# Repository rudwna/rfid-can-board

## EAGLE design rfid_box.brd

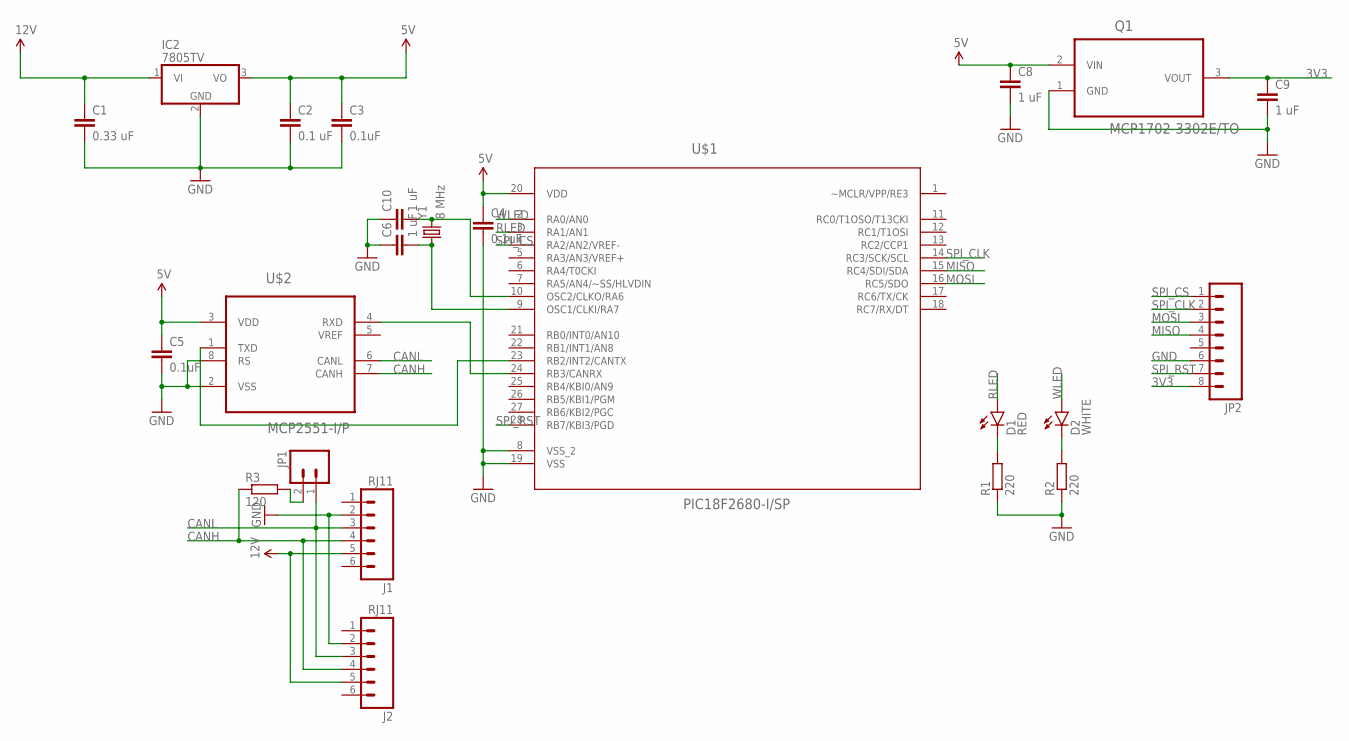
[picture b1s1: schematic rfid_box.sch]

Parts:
C1: 0.33 uF; C050-030X075
C2: 0.1 uF; C050-030X075
C3, C4, C5: 0.1uF; C050-030X075
C6, C10: 1 uF; C025-025X050
C8, C9: 1 uF; C050-030X075
D1: RED; LED5MM
D2: WHITE; LED5MM
IC2: 7805TV; TO220V
J1, J2: RJ11; RJ11-6
JP1: M02PTH; 1X02
JP2: M08; 1X08_ROUND
Q1: MCP1702-3302E/TO; TO127P254X533-3
R1, R2: 220; 0207/10
R3: 120; 0207/10
U$1: PIC18F2680-I/SP; DIP254P762X508-28
U$2: MCP2551-I/P; DIP254P762X432-8
Y1: 8 MHz; HC49US

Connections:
3V3: C9.1, JP2.8, Q1.3 (VOUT)
5V: C2.1, C3.1, C4.1, C5.1, C8.1, IC2.3 (VO), Q1.2 (VIN), U$1.20 (VDD), U$2.3 (VDD)
12V: C1.1, IC2.1 (VI), J1.5, J2.5
CANH: J1.4, J2.4, R3.1, U$2.7 (CANH)
CANL: J1.3, J2.3, JP1.1, U$2.6 (CANL)
GND: C1.2, C2.2, C3.2, C4.2, C5.2, C6.1, C8.2, C9.2, C10.1, IC2.2 (GND), J1.2, J2.2, JP2.6, Q1.1 (GND), R1.1, R2.1, U$1.8 (VSS_2), U$1.19 (VSS), U$2.2 (VSS), U$2.8 (RS)
MISO: JP2.4, U$1.15 (RC4/SDI/SDA)
MOSI: JP2.3, U$1.16 (RC5/SDO)
unnamed: U$1.24 (RB3/CANRX), U$2.4 (RXD)
unnamed: U$1.23 (RB2/INT2/CANTX), U$2.1 (TXD)
unnamed: C10.2, U$1.10 (OSC2/CLKO/RA6), Y1.2
unnamed: C6.2, U$1.9 (OSC1/CLKI/RA7), Y1.1
unnamed: D1.K (C), R1.2
unnamed: D2.K (C), R2.2
unnamed: JP1.2, R3.2
RLED: D1.A, U$1.3 (RA1/AN1)
SPI_CLK: JP2.2, U$1.14 (RC3/SCK/SCL)
SPI_CS: JP2.1, U$1.4 (RA2/AN2/VREF-)
SPI_RST: JP2.7, U$1.28 (RB7/KBI3/PGD)
WLED: D2.A, U$1.2 (RA0/AN0)

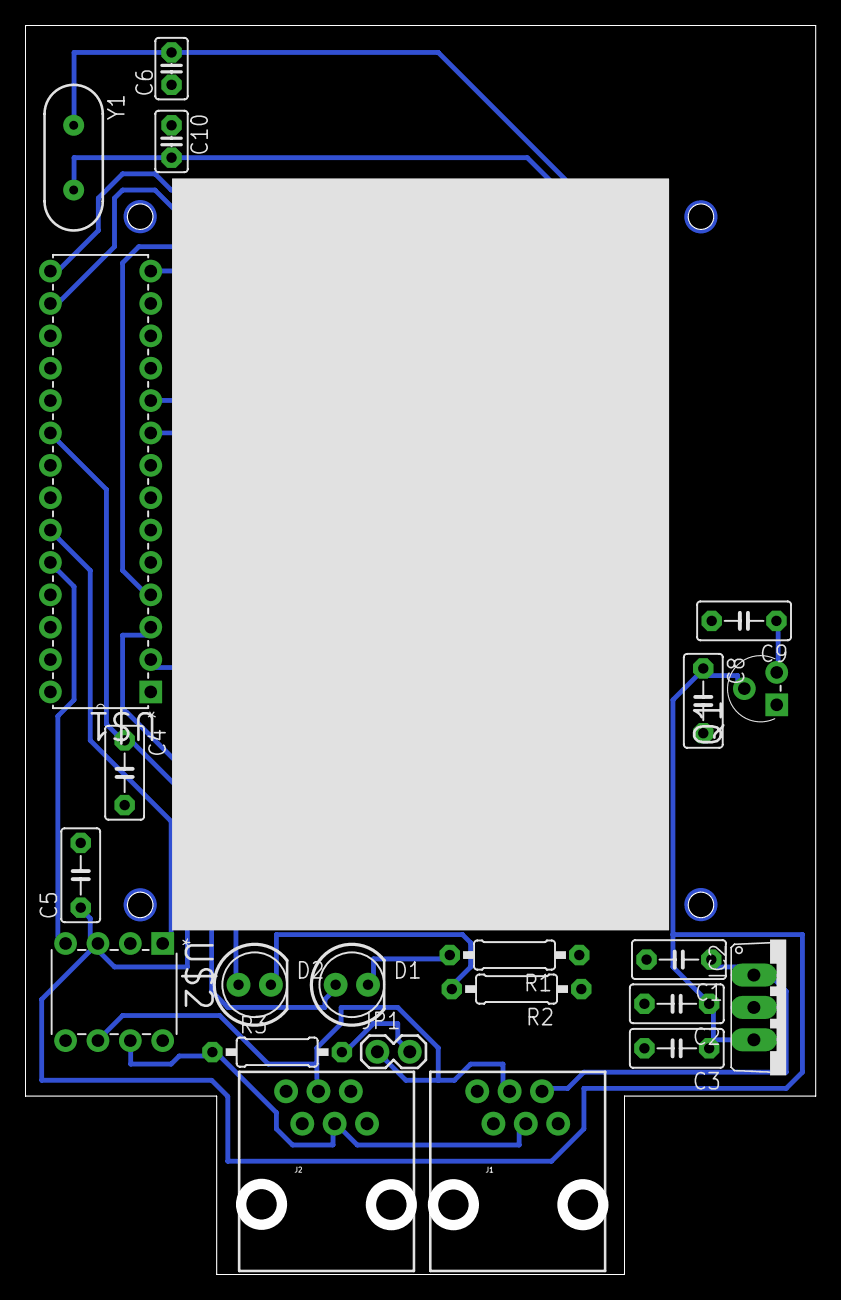
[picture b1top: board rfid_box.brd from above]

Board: 2 copper layers, 61.2 x 97.2 mm, 23 parts (0 on the bottom side), 20 nets.

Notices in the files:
parts and their libraries:
SparkFun-LED: Licensing: Creative Commons ShareAlike 4.0 International - https://creativecommons.org/licenses/by-sa/4.0
